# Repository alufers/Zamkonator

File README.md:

# Zamkonator - a PoE powered electronic lock system

**INFO**: This project is in a work in progress state and is not yet complete.

This is a repository for the hardware and software for a PoE powered locks system. It reads RFID cards using the [Wiegand interface](https://en.wikipedia.org/wiki/Wiegand_interface), and opens an electronic door latch to grant entry. This project simplifies the deployment of such systems by eliminating the need for a separate power supply for the lock. Additionally it connects directly to a LDAP server to authenticate users, thus removing any central coordination between multiple locks.

## Hardware overview

The system is based on the ESP32 SoC and the RTL8201F PHY. The PoE power supply is supplied by the [SI3404-A-GM](https://datasheet.lcsc.com/lcsc/2108241830_SILICON-LABS-SI3404-A-GMR_C461934.pdf) IC. To provide an extra layer of safety, the Wiegand interface is isolated using optocouplers and the lock is controlled via a relay to eliminate any possibility of surges occuring in long cables.

[Full PDF schematic](./schematic.pdf)

## Firmware

The firmware is located in the `zamek-firmware/` directory. To build it you will need ESP-IDF 4.4.2.

### Building

```sh
# with the ESP-IDF activated, in the zamek-firmware/ directory
idf.py build
```

Alternatively you can use included nix shell, which automatically downloads and activates the ESP-IDF.

```sh
nix develop
idf.py build
```

### Flashing

```sh
# with the ESP-IDF activated
idf.py flash
```

If you are flashing a board for the first time you will also need to flash the littlefs partition. To do that run:

```sh
./flash_littlefs.sh
```

# License

MIT

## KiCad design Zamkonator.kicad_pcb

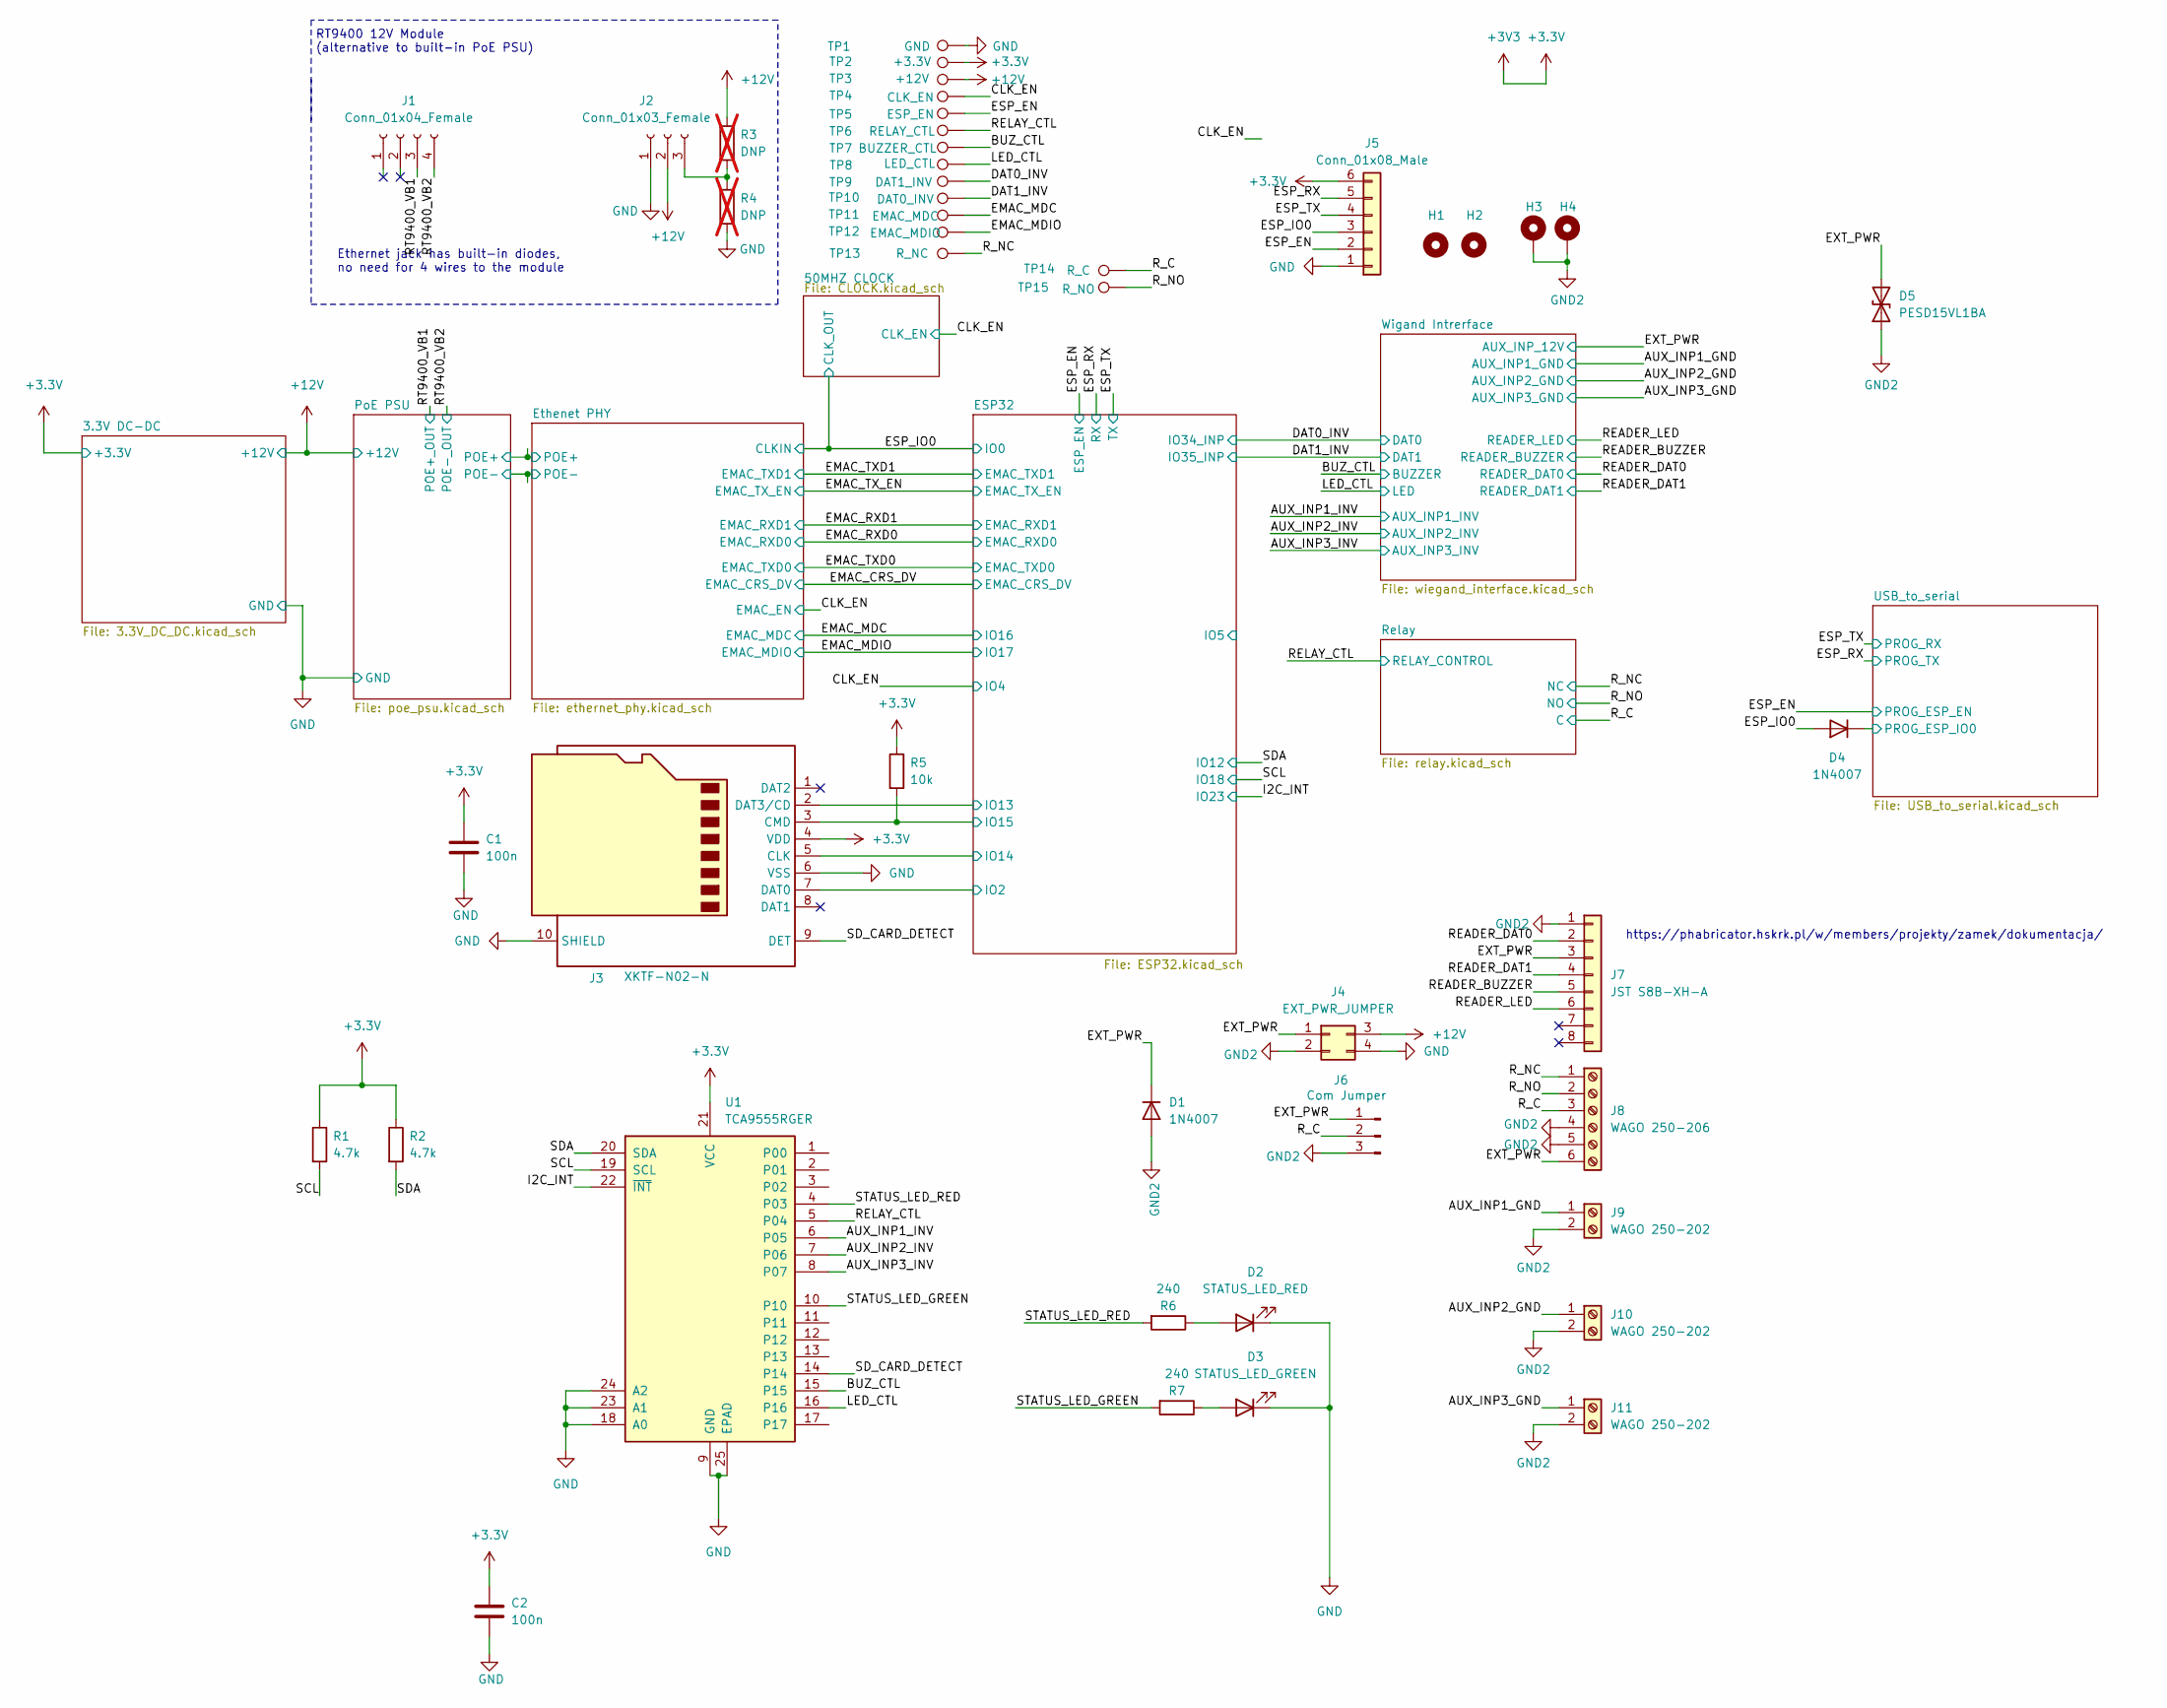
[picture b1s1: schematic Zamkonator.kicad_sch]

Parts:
C1, C2: 100n; C_0603_1608Metric_Pad1.08x0.95mm_HandSolder; LCSC C282519
D1, D4: 1N4007; D_SMA_Handsoldering; LCSC C7528875
D2: STATUS_LED_RED; LED_0603_1608Metric; LCSC C2286
D3: STATUS_LED_GREEN; LED_0603_1608Metric; LCSC C916074
D5: PESD15VL1BA; D_SOD-323; LCSC C18723438
H1, H2: MountingHole_Pad; MountingHole_3.2mm_M3
H3, H4: MountingHole_Pad; MountingHole_3.2mm_M3_Pad_Via
J1: Conn_01x04_Female; PinSocket_1x04_P2.54mm_Vertical; LCSC C2718488
J2: Conn_01x03_Female; PinSocket_1x03_P2.54mm_Vertical; LCSC C7509516
J3: XKTF-N02-N; TF-SMD_XKTF-N02-N; LCSC C381084
J4: EXT_PWR_JUMPER; PinHeader_2x02_P2.54mm_Vertical; LCSC C7501273
J5: Conn_01x08_Male; PinHeader_1x06_P2.54mm_Vertical; LCSC C37208
J6: Com Jumper; PinHeader_1x03_P2.54mm_Vertical; LCSC C2937625
J7: JST S8B-XH-A; JST_XH_S8B-XH-A_1x08_P2.50mm_Horizontal; LCSC C157914
J8: WAGO 250-206; CONN-TH_250-206; LCSC C7470120
J9, J10, J11: WAGO 250-202; CONN-TH_250-202; LCSC C5443567
R1, R2: 4.7k; R_0603_1608Metric_Pad0.98x0.95mm_HandSolder; LCSC C2907166
R3, R4: DNP; R_0603_1608Metric_Pad0.98x0.95mm_HandSolder; not fitted
R5: 10k; R_0603_1608Metric_Pad0.98x0.95mm_HandSolder; LCSC C2930027
R6, R7: 240; R_0603_1608Metric_Pad0.98x0.95mm_HandSolder; LCSC C2907130
TP1: GND; TestPoint_Pad_D3.0mm
TP2: +3.3V; TestPoint_Pad_D3.0mm
TP3: +12V; TestPoint_Pad_D3.0mm
TP4: CLK_EN; TestPoint_Pad_D1.5mm
TP5: ESP_EN; TestPoint_Pad_D1.5mm
TP6: RELAY_CTL; TestPoint_Pad_D1.5mm
TP7: BUZZER_CTL; TestPoint_Pad_D1.5mm
TP8: LED_CTL; TestPoint_Pad_D1.5mm
TP9: DAT1_INV; TestPoint_Pad_D1.5mm
TP10: DAT0_INV; TestPoint_Pad_D1.5mm
TP11: EMAC_MDC; TestPoint_Pad_D1.5mm
TP12: EMAC_MDIO; TestPoint_Pad_D1.5mm
TP13: R_NC; TestPoint_Pad_D3.0mm
TP14: R_C; TestPoint_Pad_D3.0mm
TP15: R_NO; TestPoint_Pad_D3.0mm
U1: TCA9555RGER; VQFN-24-1EP_4x4mm_P0.5mm_EP2.45x2.45mm; LCSC C42420609

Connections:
+3.3V: C1.1, C2.1, J3.4 (VDD), J5.6, R1.1, R2.1, R5.1, TP2.1 (1_1), U1.21 (VCC); also elsewhere on the board
+12V: J2.2, J4.3, R3.1, TP3.1 (1_1); also elsewhere on the board
/AUX_INP1_GND: J9.1; also elsewhere on the board
/AUX_INP1_INV: U1.6 (P05); also elsewhere on the board
/AUX_INP2_GND: J10.1; also elsewhere on the board
/AUX_INP2_INV: U1.7 (P06); also elsewhere on the board
/AUX_INP3_GND: J11.1; also elsewhere on the board
/AUX_INP3_INV: U1.8 (P07); also elsewhere on the board
/BUZ_CTL: TP7.1 (1_1), U1.15; also elsewhere on the board
/CLK_EN: TP4.1 (1_1); also elsewhere on the board
/DAT0_INV: TP9.1 (1_1); also elsewhere on the board
/DAT1_INV: TP10.1 (1_1); also elsewhere on the board
/EMAC_MDC: TP11.1 (1_1); also elsewhere on the board
/EMAC_MDIO: TP12.1 (1_1); also elsewhere on the board
/ESP32/IO2: J3.7 (DAT0); also elsewhere on the board
/ESP32/IO13: J3.2 (DAT3/CD); also elsewhere on the board
/ESP32/IO14: J3.5 (CLK); also elsewhere on the board
/ESP32/IO15: J3.3 (CMD), R5.2; also elsewhere on the board
/ESP_EN: J5.2, TP5.1 (1_1); also elsewhere on the board
/ESP_IO0: D4.2 (A), J5.3; also elsewhere on the board
/ESP_RX: J5.5; also elsewhere on the board
/ESP_TX: J5.4; also elsewhere on the board
/EXT_PWR: D1.1 (K), D5.2 (A2), J4.1, J6.1, J7.3, J8.6; also elsewhere on the board
/I2C_INT: U1.22 (~INT); also elsewhere on the board
/LED_CTL: TP8.1 (1_1), U1.16; also elsewhere on the board
/READER_BUZZER: J7.5; also elsewhere on the board
/READER_DAT0: J7.2; also elsewhere on the board
/READER_DAT1: J7.4; also elsewhere on the board
/READER_LED: J7.6; also elsewhere on the board
/RELAY_CTL: TP6.1 (1_1), U1.5 (P04); also elsewhere on the board
/RT9400_VB1: J1.3; also elsewhere on the board
/RT9400_VB2: J1.4; also elsewhere on the board
/R_C: J6.2, J8.3, TP14.1 (1_1); also elsewhere on the board
/R_NC: J8.1, TP13.1 (1_1); also elsewhere on the board
/R_NO: J8.2, TP15.1 (1_1); also elsewhere on the board
/SCL: R1.2, U1.19 (SCL); also elsewhere on the board
/SDA: R2.2, U1.20 (SDA); also elsewhere on the board
/SD_CARD_DETECT: J3.9 (DET), U1.14
/STATUS_LED_GREEN: R7.2, U1.10
/STATUS_LED_RED: R6.2, U1.4 (P03)
/USB_to_serial/PROG_ESP_IO0: D4.1 (K); also elsewhere on the board
GND: C1.2, C2.2, D2.1 (K), D3.1 (K), J2.1, J3.6 (VSS), J3.10 (SHIELD), J4.4, J5.1, R4.2, TP1.1 (1_1), U1.9 (GND), U1.18 (A0), U1.23 (A1), U1.24 (A2), U1.25 (EPAD); also elsewhere on the board
GND2: D1.2 (A), D5.1 (A1), H3.1 (1_1), H4.1 (1_1), J4.2, J6.3, J7.1, J8.4, J8.5, J9.2, J10.2, J11.2; also elsewhere on the board
unnamed: D2.2 (A), R6.1
unnamed: D3.2 (A), R7.1
unnamed: J2.3, R3.2, R4.1

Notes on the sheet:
RT9400 12V Module (alternative to built-in PoE PSU)
Ethernet jack has built-in diodes, no need for 4 wires to the module
https://phabricator.hskrk.pl/w/members/projekty/zamek/dokumentacja/

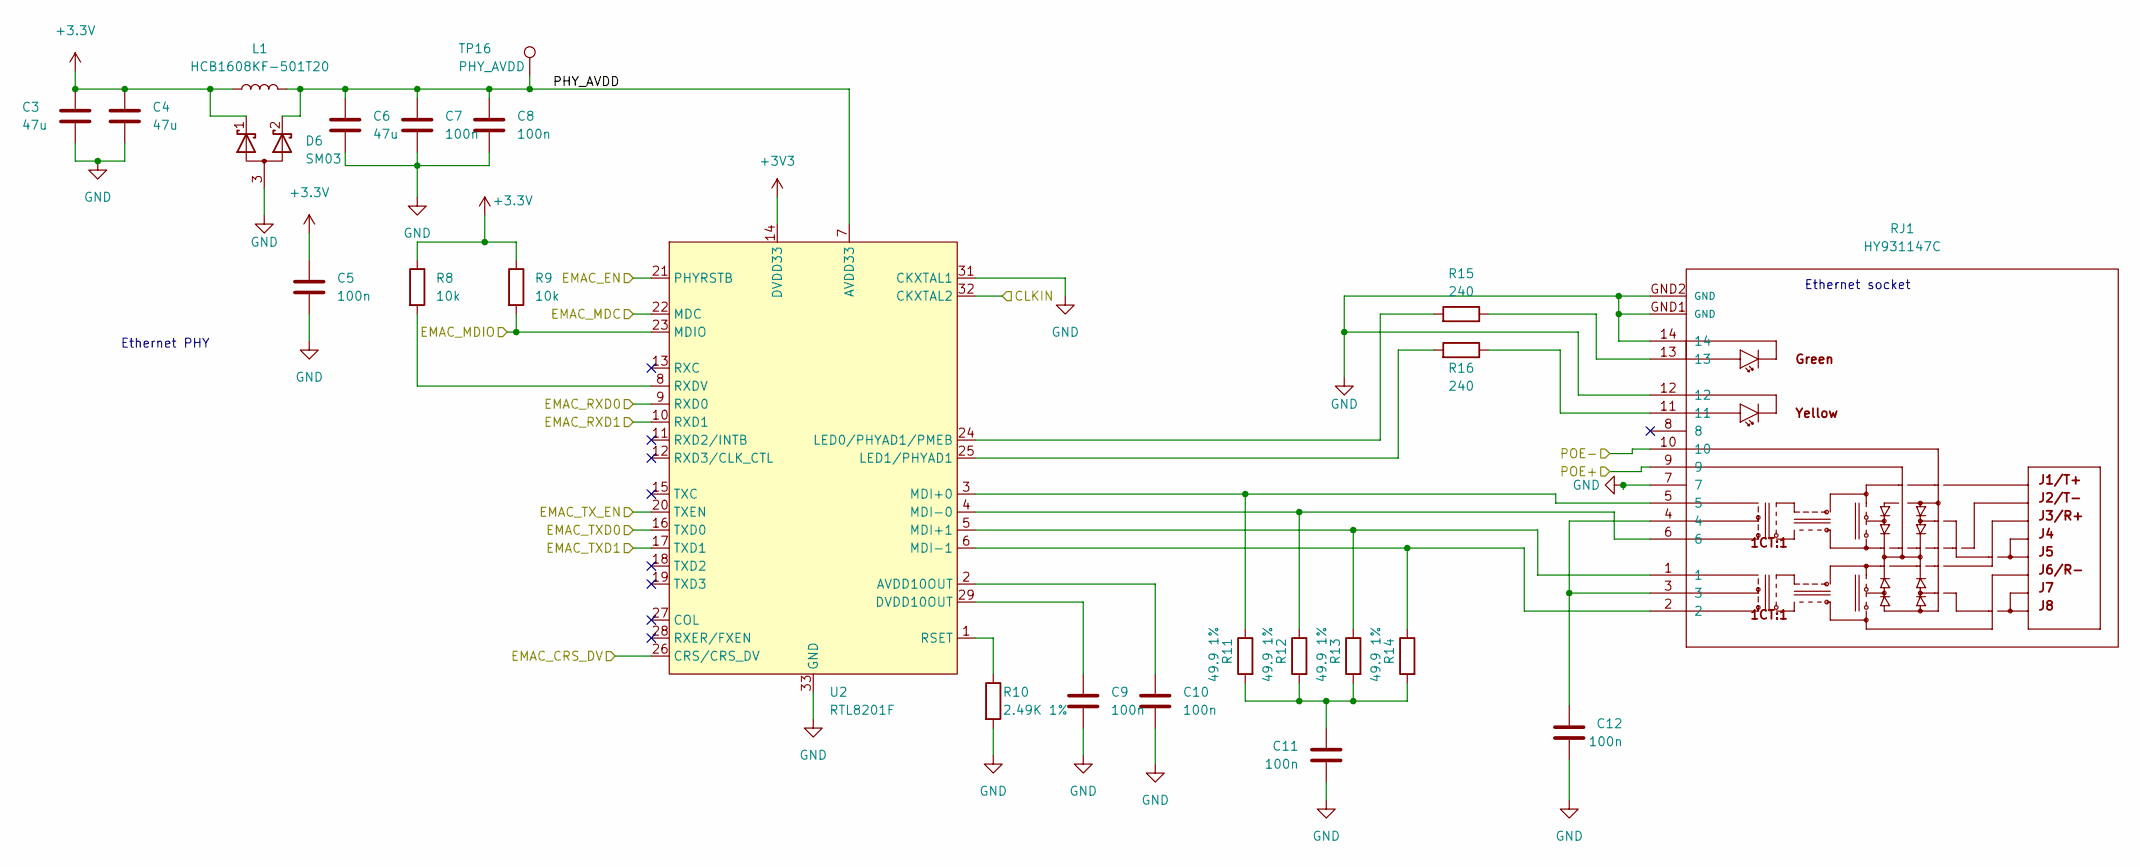
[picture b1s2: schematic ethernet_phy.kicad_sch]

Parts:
C3, C4, C6: 47u; C_0603_1608Metric_Pad1.08x0.95mm_HandSolder; LCSC C140782
C5, C7, C8, C9, C10, C11, C12: 100n; C_0603_1608Metric_Pad1.08x0.95mm_HandSolder; LCSC C282519
D6: SM03; TSOT-23_HandSoldering; LCSC C502558
L1: HCB1608KF-501T20; L_0603_1608Metric; LCSC C356979
R8, R9: 10k; R_0603_1608Metric_Pad0.98x0.95mm_HandSolder; LCSC C2930027
R10: 2.49K 1%; R_0603_1608Metric_Pad0.98x0.95mm_HandSolder; LCSC C100897
R11, R12, R13, R14: 49.9 1%; R_0603_1608Metric_Pad0.98x0.95mm_HandSolder; LCSC C114625
R15, R16: 240; R_0603_1608Metric_Pad0.98x0.95mm_HandSolder; LCSC C2907130
RJ1: HY931147C; RJ45-TH_HY931147C; LCSC C91754
TP16: PHY_AVDD; TestPoint_Pad_D1.5mm
U2: RTL8201F; QFN-32-1EP_5x5mm_P0.5mm_EP3.3x3.3mm; LCSC C45044

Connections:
+3.3V: C3.1, C4.1, C5.1, D6.1 (K), L1.1, R8.1, R9.1, U2.14 (DVDD33); also elsewhere on the board
/CLK_EN: U2.21 (PHYRSTB); also elsewhere on the board
/EMAC_CRS_DV: U2.26 (CRS/CRS_DV); also elsewhere on the board
/EMAC_MDC: U2.22 (MDC); also elsewhere on the board
/EMAC_MDIO: R9.2, U2.23 (MDIO); also elsewhere on the board
/EMAC_RXD0: U2.9 (RXD0); also elsewhere on the board
/EMAC_RXD1: U2.10 (RXD1); also elsewhere on the board
/EMAC_TXD0: U2.16 (TXD0); also elsewhere on the board
/EMAC_TXD1: U2.17 (TXD1); also elsewhere on the board
/EMAC_TX_EN: U2.20 (TXEN); also elsewhere on the board
/ESP_IO0: U2.32 (CKXTAL2); also elsewhere on the board
/Ethenet PHY/PHY_AVDD: C6.1, C7.1, C8.1, D6.2 (K), L1.2, TP16.1 (1_1), U2.7 (AVDD33), U2.30 (AVDD33)
/Ethenet PHY/POE+: RJ1.9; also elsewhere on the board
/Ethenet PHY/POE-: RJ1.10; also elsewhere on the board
GND: C3.2, C4.2, C5.2, C6.2, C7.2, C8.2, C9.2, C10.2, C11.2, C12.2, D6.3 (A), R10.2, RJ1.7, RJ1.12, RJ1.14, RJ1.GND1 (GND), RJ1.GND2 (GND), U2.31 (CKXTAL1), U2.33 (GND); also elsewhere on the board
unnamed: C11.1, R11.2, R12.2, R13.2, R14.2
unnamed: C12.1, RJ1.3, RJ1.4
unnamed: R15.1, RJ1.13
unnamed: R16.1, RJ1.11
unnamed: C10.1, U2.2 (AVDD10OUT)
unnamed: C9.1, U2.29 (DVDD10OUT)
unnamed: R15.2, U2.24 (LED0/PHYAD1/PMEB)
unnamed: R16.2, U2.25 (LED1/PHYAD1)
unnamed: R11.1, RJ1.5, U2.3 (MDI+0)
unnamed: R13.1, RJ1.1, U2.5 (MDI+1)
unnamed: R12.1, RJ1.6, U2.4 (MDI-0)
unnamed: R14.1, RJ1.2, U2.6 (MDI-1)
unnamed: R10.1, U2.1 (RSET)
unnamed: R8.2, U2.8 (RXDV)

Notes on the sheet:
Ethernet socket
Ethernet PHY

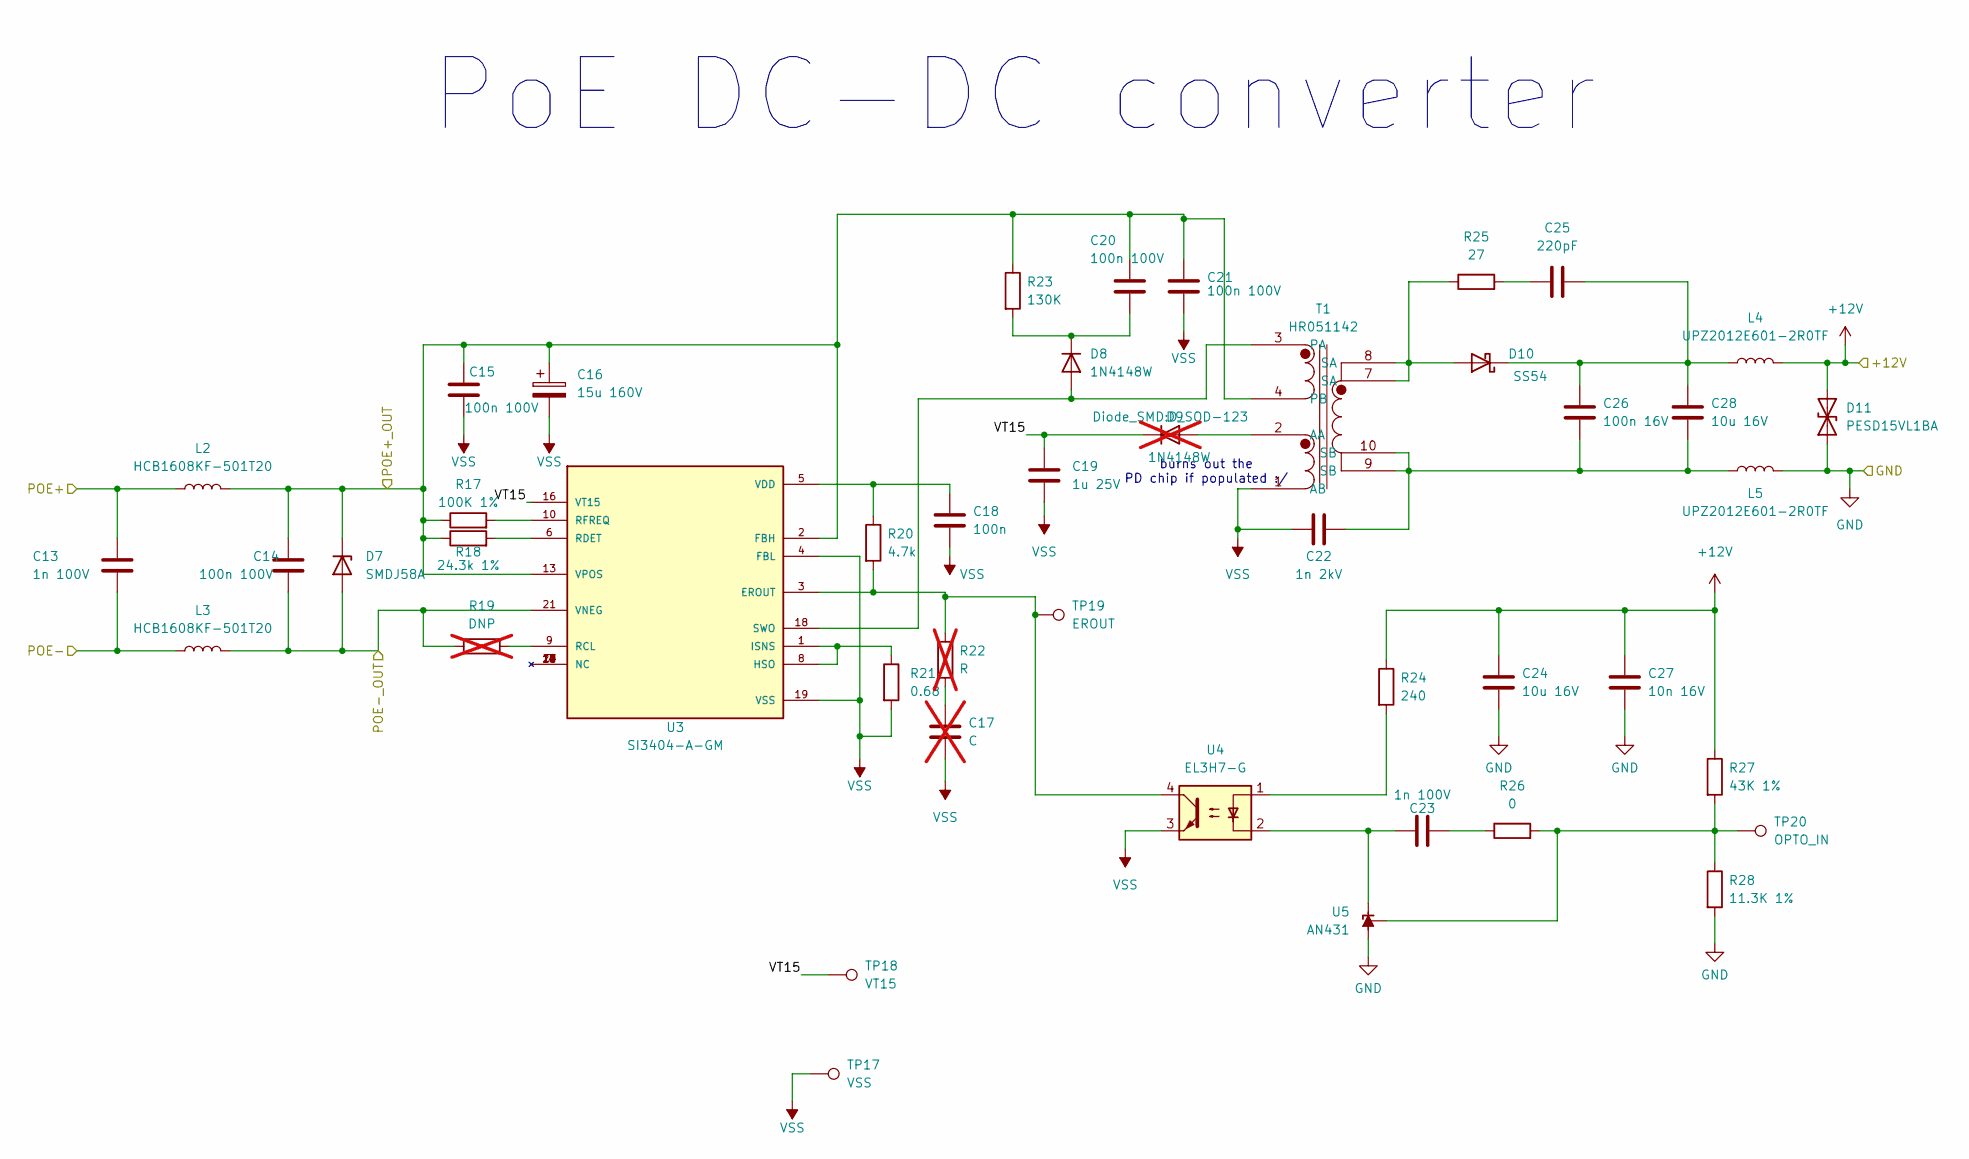
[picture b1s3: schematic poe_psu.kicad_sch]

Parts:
C13, C23: 1n 100V; C_0603_1608Metric_Pad1.08x0.95mm_HandSolder; LCSC C282513
C14, C15, C20, C21: 100n 100V; C_0603_1608Metric_Pad1.08x0.95mm_HandSolder; LCSC C696916
C16: 15u 160V; CP_Elec_10x10.5; LCSC C98557
C17: C; C_0603_1608Metric_Pad1.08x0.95mm_HandSolder; not fitted
C18: 100n; C_0603_1608Metric_Pad1.08x0.95mm_HandSolder; LCSC C282519
C19: 1u 25V; C_0603_1608Metric_Pad1.08x0.95mm_HandSolder; LCSC C5673
C22: 1n 2kV; C_1206_3216Metric_Pad1.33x1.80mm_HandSolder; LCSC C363565
C24, C28: 10u 16V; C_0603_1608Metric_Pad1.08x0.95mm_HandSolder; LCSC C92487
C25: 220pF; C_0603_1608Metric_Pad1.08x0.95mm_HandSolder; LCSC C2760542
C26: 100n 16V; C_0603_1608Metric_Pad1.08x0.95mm_HandSolder; LCSC C696916
C27: 10n 16V; C_0603_1608Metric_Pad1.08x0.95mm_HandSolder; LCSC C163173
D7: SMDJ58A; D_SMB-SMC_Universal_Handsoldering; LCSC C4154735
D8: 1N4148W; D_SOD-123; LCSC C444720
D9: 1N4148W; D_SOD-123; LCSC C181133; not fitted
D10: SS54; D_SMA_Handsoldering; LCSC C513478
D11: PESD15VL1BA; D_SOD-323; LCSC C18723438
L2, L3: HCB1608KF-501T20; L_0603_1608Metric; LCSC C356979
L4, L5: UPZ2012E601-2R0TF; L_0805_2012Metric_Pad1.15x1.40mm_HandSolder; LCSC C98308
R17: 100K 1%; R_0603_1608Metric_Pad0.98x0.95mm_HandSolder; LCSC C2906980
R18: 24.3k 1%; R_0603_1608Metric_Pad0.98x0.95mm_HandSolder; LCSC C276290
R19: DNP; R_0603_1608Metric_Pad0.98x0.95mm_HandSolder; not fitted
R20: 4.7k; R_0603_1608Metric_Pad0.98x0.95mm_HandSolder; LCSC C2907166
R21: 0.68; R_0603_1608Metric_Pad0.98x0.95mm_HandSolder; LCSC C5126107
R22: R; R_0603_1608Metric_Pad0.98x0.95mm_HandSolder; not fitted
R23: 130K; R_0603_1608Metric_Pad0.98x0.95mm_HandSolder; LCSC C2906991
R24: 240; R_0603_1608Metric_Pad0.98x0.95mm_HandSolder; LCSC C2907130
R25: 27; R_0603_1608Metric_Pad0.98x0.95mm_HandSolder; LCSC C5140675
R26: 0; R_0603_1608Metric_Pad0.98x0.95mm_HandSolder; LCSC C100044
R27: 43K 1%; R_0603_1608Metric_Pad0.98x0.95mm_HandSolder; LCSC C137719
R28: 11.3K 1%; R_0603_1608Metric_Pad0.98x0.95mm_HandSolder; LCSC C137803
T1: HR051142; LCSC C55680
TP17: VSS; TestPoint_Pad_D1.5mm
TP18: VT15; TestPoint_Pad_D1.5mm
TP19: EROUT; TestPoint_Pad_D1.5mm
TP20: OPTO_IN; TestPoint_Pad_D1.5mm
U3: SI3404-A-GM; MLF-20-1EP_4x4mm_P0.5mm_EP2.6x2.6mm_ThermalVias; PARTREV 1.0; LCSC C461934
U4: EL3H7-G; SSOP-4_4.4x2.6mm_P1.27mm; LCSC C92243
U5: AN431; SOT-23; LCSC C97717

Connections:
+12V: C24.1, C27.1, D11.2 (A2), L4.2, R24.1, R27.1; also elsewhere on the board
/Ethenet PHY/POE+: C13.1, L2.1; also elsewhere on the board
/Ethenet PHY/POE-: C13.2, L3.1; also elsewhere on the board
/PoE PSU/VT15: C19.1, D9.1 (K), TP18.1 (1_1), U3.16 (VT15)
/RT9400_VB1: C14.1, C15.1, C16.1, C20.1, C21.1, D7.1 (K), L2.2, R17.1, R18.1, R23.1, T1.4 (PB), U3.2 (FBH), U3.13 (VPOS); also elsewhere on the board
/RT9400_VB2: C14.2, D7.2 (A), L3.2, R19.1, U3.21 (VNEG); also elsewhere on the board
GND: C24.2, C27.2, D11.1 (A1), L5.2, R28.2, U5.3 (A); also elsewhere on the board
unnamed: C17.1, R22.2
unnamed: C22.2, C26.2, C28.2, L5.1, T1.9 (SB), T1.10 (SB)
unnamed: C23.2, R26.1
unnamed: C25.1, R25.2
unnamed: D8.2 (A), T1.3 (PA), U3.18 (SWO)
unnamed: C20.2, D8.1 (K), R23.2
unnamed: D9.2 (A), T1.2 (AA)
unnamed: D10.2 (A), R25.1, T1.7 (SA), T1.8 (SA)
unnamed: C25.2, C26.1, C28.1, D10.1 (K), L4.1
unnamed: R24.2, U4.1
unnamed: R20.2, R22.1, TP19.1 (1_1), U3.3 (EROUT), U4.4
unnamed: R21.1, U3.1 (ISNS), U3.8 (HSO)
unnamed: R19.2, U3.9 (RCL)
unnamed: R18.2, U3.6 (RDET)
unnamed: R17.2, U3.10 (RFREQ)
unnamed: C18.1, R20.1, U3.5 (VDD)
unnamed: C23.1, U4.2, U5.1 (K)
unnamed: R26.2, R27.2, R28.1, TP20.1 (1_1), U5.2 (REF)
VSS: C15.2, C16.2, C17.2, C18.2, C19.2, C21.2, C22.1, R21.2, T1.1 (AB), TP17.1 (1_1), U3.4 (FBL), U3.19 (VSS), U4.3

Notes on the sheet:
PoE DC-DC converter
burns out the PD chip if populated :/

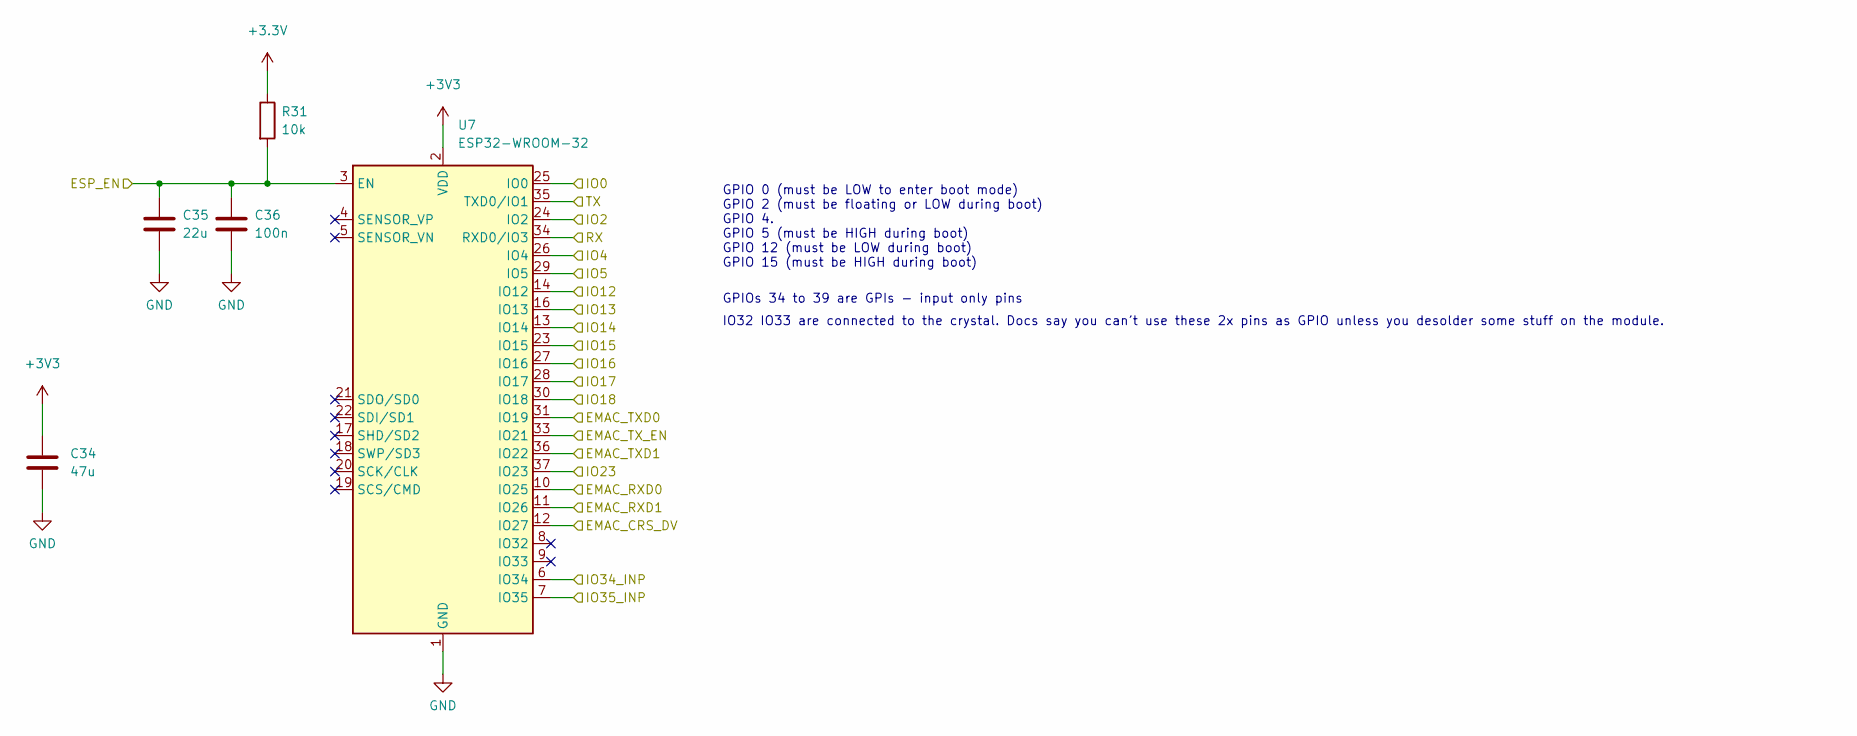
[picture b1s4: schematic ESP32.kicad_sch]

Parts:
C34: 47u; C_0603_1608Metric_Pad1.08x0.95mm_HandSolder; LCSC C140782
C35: 22u; C_0603_1608Metric_Pad1.08x0.95mm_HandSolder; LCSC C59461
C36: 100n; C_0603_1608Metric_Pad1.08x0.95mm_HandSolder; LCSC C282519
R31: 10k; R_0603_1608Metric_Pad0.98x0.95mm_HandSolder; LCSC C2930027
U7: ESP32-WROOM-32; LCSC C473012

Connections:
+3.3V: C34.1, R31.1, U7.2 (VDD); also elsewhere on the board
/CLK_EN: U7.26 (IO4); also elsewhere on the board
/DAT0_INV: U7.6 (IO34); also elsewhere on the board
/DAT1_INV: U7.7 (IO35); also elsewhere on the board
/EMAC_CRS_DV: U7.12 (IO27); also elsewhere on the board
/EMAC_MDC: U7.27 (IO16); also elsewhere on the board
/EMAC_MDIO: U7.28 (IO17); also elsewhere on the board
/EMAC_RXD0: U7.10 (IO25); also elsewhere on the board
/EMAC_RXD1: U7.11 (IO26); also elsewhere on the board
/EMAC_TXD0: U7.31 (IO19); also elsewhere on the board
/EMAC_TXD1: U7.36 (IO22); also elsewhere on the board
/EMAC_TX_EN: U7.33 (IO21); also elsewhere on the board
/ESP32/IO2: U7.24 (IO2); also elsewhere on the board
/ESP32/IO5: U7.29 (IO5)
/ESP32/IO13: U7.16 (IO13); also elsewhere on the board
/ESP32/IO14: U7.13 (IO14); also elsewhere on the board
/ESP32/IO15: U7.23 (IO15); also elsewhere on the board
/ESP_EN: C35.1, C36.1, R31.2, U7.3 (EN); also elsewhere on the board
/ESP_IO0: U7.25 (IO0); also elsewhere on the board
/ESP_RX: U7.34 (RXD0/IO3); also elsewhere on the board
/ESP_TX: U7.35 (TXD0/IO1); also elsewhere on the board
/I2C_INT: U7.37 (IO23); also elsewhere on the board
/SCL: U7.30 (IO18); also elsewhere on the board
/SDA: U7.14 (IO12); also elsewhere on the board
GND: C34.2, C35.2, C36.2, U7.1 (GND), U7.15 (GND), U7.38 (GND), U7.39 (GND); also elsewhere on the board

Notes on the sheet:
IO32 IO33 are connected to the crystal. Docs say you can't use these 2x pins as GPIO unless you desolder some stuff on the module.
GPIOs 34 to 39 are GPIs - input only pins
GPIO 0 (must be LOW to enter boot mode) GPIO 2 (must be floating or LOW during boot) GPIO 4. GPIO 5 (must be HIGH during boot) GPIO 12 (must be LOW during boot) GPIO 15 (must be HIGH during boot)

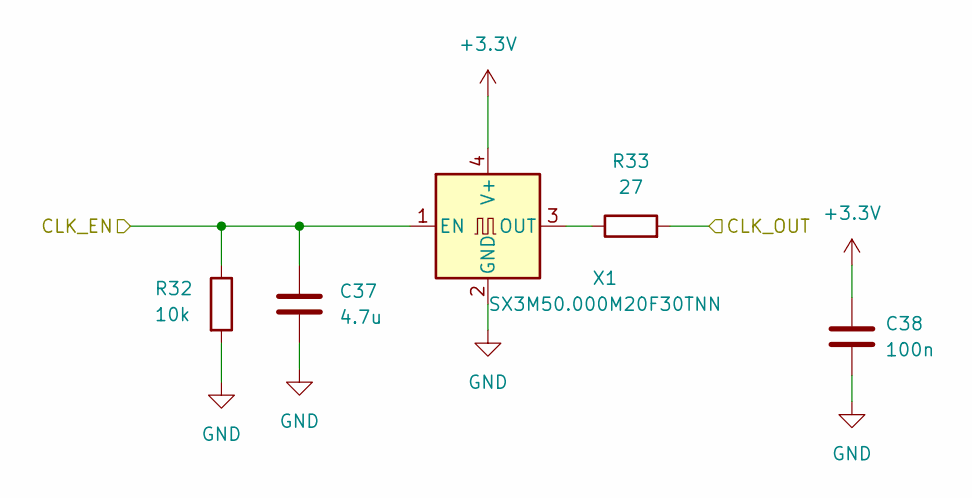
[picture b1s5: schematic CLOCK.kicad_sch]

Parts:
C37: 4.7u; C_0603_1608Metric_Pad1.08x0.95mm_HandSolder; LCSC C8032
C38: 100n; C_0603_1608Metric_Pad1.08x0.95mm_HandSolder; LCSC C282519
R32: 10k; R_0603_1608Metric_Pad0.98x0.95mm_HandSolder; LCSC C2930027
R33: 27; R_0603_1608Metric_Pad0.98x0.95mm_HandSolder; LCSC C5140675
X1: SX3M50.000M20F30TNN; Oscillator_SMD_EuroQuartz_XO32-4Pin_3.2x2.5mm; LCSC C2901592

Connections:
+3.3V: C38.1, X1.4 (V+); also elsewhere on the board
/CLK_EN: C37.1, R32.1, X1.1 (EN); also elsewhere on the board
/ESP_IO0: R33.2; also elsewhere on the board
GND: C37.2, C38.2, R32.2, X1.2 (GND); also elsewhere on the board
unnamed: R33.1, X1.3 (OUT)

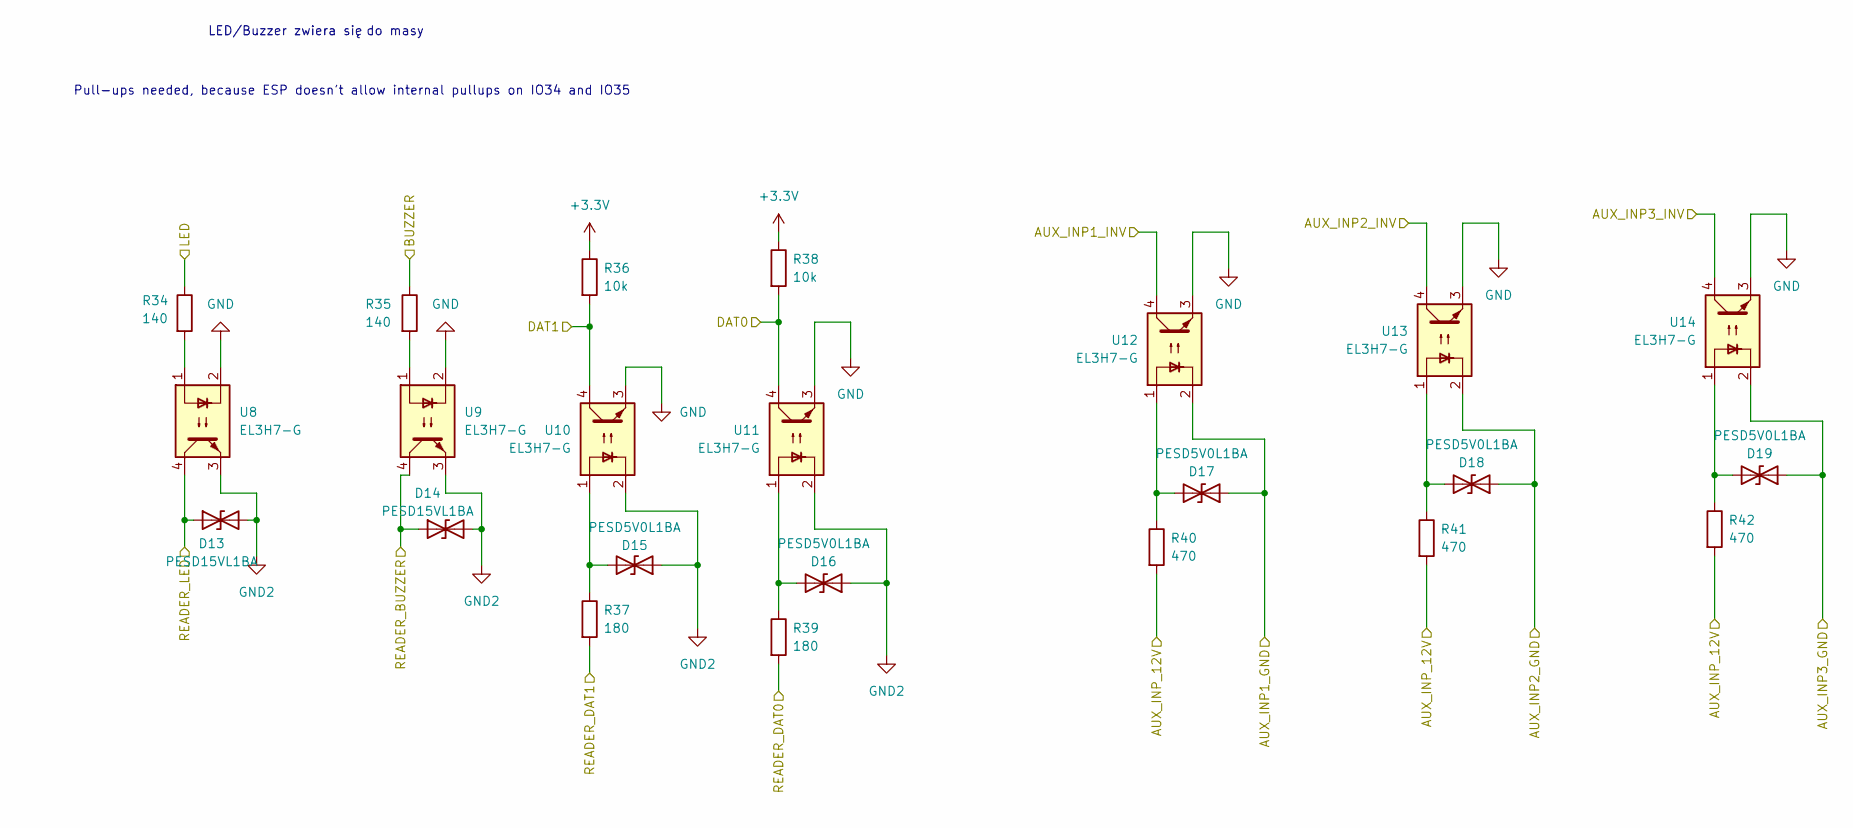
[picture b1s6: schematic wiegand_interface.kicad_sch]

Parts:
D13, D14: PESD15VL1BA; D_SOD-323; LCSC C18723438
D15, D16, D17, D18, D19: PESD5V0L1BA; D_SOD-323; LCSC C85380
R34, R35: 140; R_0603_1608Metric_Pad0.98x0.95mm_HandSolder; LCSC C2974027
R36, R38: 10k; R_0603_1608Metric_Pad0.98x0.95mm_HandSolder; LCSC C2930027
R37, R39: 180; R_0603_1608Metric_Pad0.98x0.95mm_HandSolder; LCSC C5140972
R40, R41, R42: 470; R_0603_1608Metric_Pad0.98x0.95mm_HandSolder; LCSC C2907172
U8, U9, U10, U11, U12, U13, U14: EL3H7-G; SSOP-4_4.4x2.6mm_P1.27mm; LCSC C92243

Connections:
+3.3V: R36.1, R38.1; also elsewhere on the board
/AUX_INP1_GND: D17.1 (A1), U12.2; also elsewhere on the board
/AUX_INP1_INV: U12.4; also elsewhere on the board
/AUX_INP2_GND: D18.1 (A1), U13.2; also elsewhere on the board
/AUX_INP2_INV: U13.4; also elsewhere on the board
/AUX_INP3_GND: D19.1 (A1), U14.2; also elsewhere on the board
/AUX_INP3_INV: U14.4; also elsewhere on the board
/BUZ_CTL: R35.1; also elsewhere on the board
/DAT0_INV: R38.2, U11.4; also elsewhere on the board
/DAT1_INV: R36.2, U10.4; also elsewhere on the board
/EXT_PWR: R40.2, R41.2, R42.2; also elsewhere on the board
/LED_CTL: R34.1; also elsewhere on the board
/READER_BUZZER: D14.1 (A1), U9.4; also elsewhere on the board
/READER_DAT0: R39.2; also elsewhere on the board
/READER_DAT1: R37.2; also elsewhere on the board
/READER_LED: D13.1 (A1), U8.4; also elsewhere on the board
GND: U8.2, U9.2, U10.3, U11.3, U12.3, U13.3, U14.3; also elsewhere on the board
GND2: D13.2 (A2), D14.2 (A2), D15.1 (A1), D16.1 (A1), U8.3, U9.3, U10.2, U11.2; also elsewhere on the board
unnamed: D15.2 (A2), R37.1, U10.1
unnamed: D16.2 (A2), R39.1, U11.1
unnamed: D17.2 (A2), R40.1, U12.1
unnamed: D18.2 (A2), R41.1, U13.1
unnamed: D19.2 (A2), R42.1, U14.1
unnamed: R34.2, U8.1
unnamed: R35.2, U9.1

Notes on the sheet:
LED/Buzzer zwiera się do masy
Pull-ups needed, because ESP doesn't allow internal pullups on IO34 and IO35

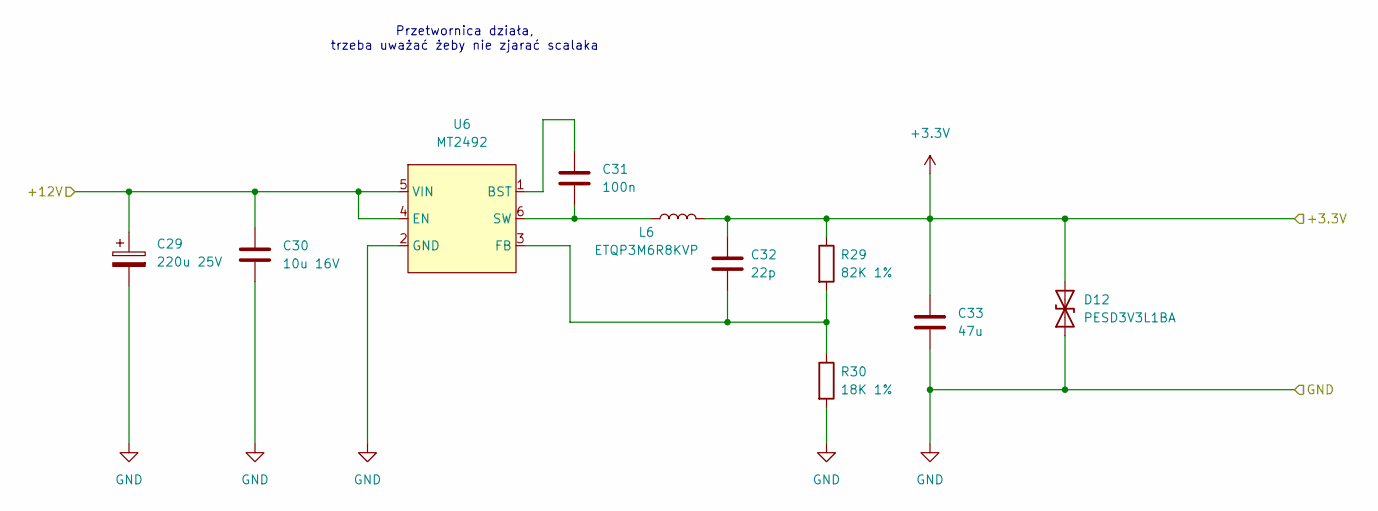
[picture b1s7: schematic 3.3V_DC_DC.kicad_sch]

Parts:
C29: 220u 25V; CP_Elec_6.3x7.7; LCSC C4747974
C30: 10u 16V; C_0603_1608Metric_Pad1.08x0.95mm_HandSolder; LCSC C92487
C31: 100n; C_0603_1608Metric_Pad1.08x0.95mm_HandSolder; LCSC C282519
C32: 22p; C_0603_1608Metric_Pad1.08x0.95mm_HandSolder; LCSC C376775
C33: 47u; C_0603_1608Metric_Pad1.08x0.95mm_HandSolder; LCSC C140782
D12: PESD3V3L1BA; D_SOD-323; LCSC C2687129
L6: ETQP3M6R8KVP; IND_PCC-M0530M-LP_PAN; LCSC C412311
R29: 82K 1%; R_0603_1608Metric_Pad0.98x0.95mm_HandSolder; LCSC C5140983
R30: 18K 1%; R_0603_1608Metric_Pad0.98x0.95mm_HandSolder; LCSC C2907001
U6: MT2492; SOT-23-6; LCSC C89358

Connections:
+3.3V: C32.1, C33.1, D12.2 (A2), L6.2, R29.1; also elsewhere on the board
+12V: C29.1, C30.1, U6.4 (EN), U6.5 (VIN); also elsewhere on the board
GND: C29.2, C30.2, C33.2, D12.1 (A1), R30.2, U6.2 (GND); also elsewhere on the board
unnamed: C31.1, U6.1 (BST)
unnamed: C32.2, R29.2, R30.1, U6.3 (FB)
unnamed: C31.2, L6.1, U6.6 (SW)

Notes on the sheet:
Przetwornica działa, trzeba uważać żeby nie zjarać scalaka
